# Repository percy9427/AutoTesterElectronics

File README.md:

# AutoTesterElectronics
This contains the Schematics and Board layout for the PCB for the autotester.  The autotester is a machine for automatically testing your water.

Info on the autotester can be found at https://robogardens.com/?p=928.

How you want to generate the PCB is up to you.  I use oshpark.com which requires simply uploading the .brd file.

A video showing the autotester in operation can be found at https://youtu.be/JWSlSH5BVns.

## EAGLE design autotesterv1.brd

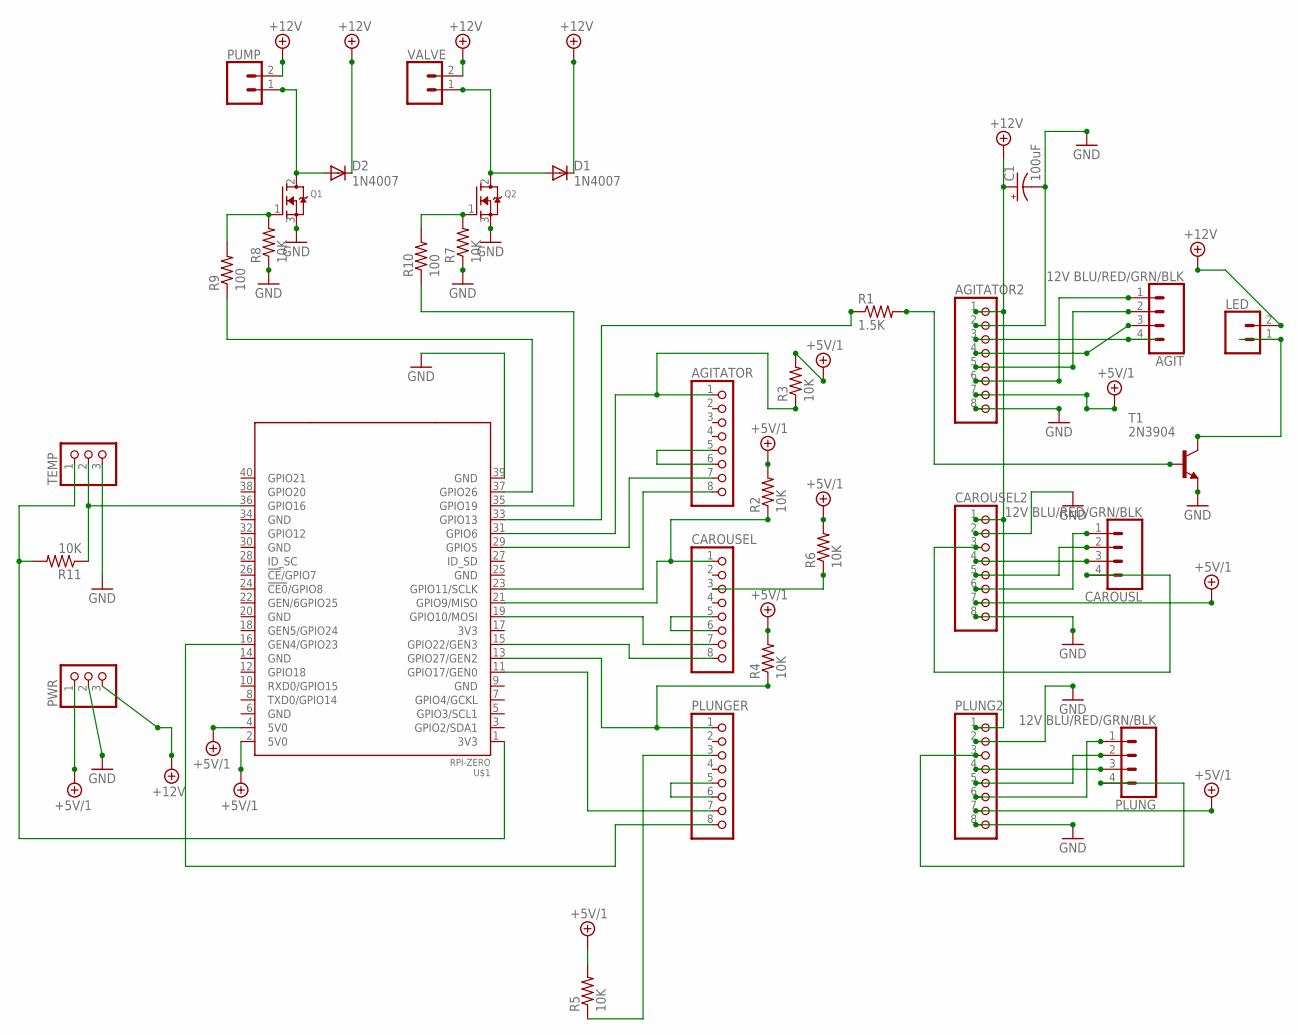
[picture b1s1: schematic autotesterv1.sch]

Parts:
AGIT: 12V BLU/RED/GRN/BLK; SCREWTERMINAL-3.5MM-4
AGITATOR, AGITATOR2: PINHD-1X8; 1X08
C1: 100uF; CPOL-RADIAL-5MM-10MM
CAROUSEL, CAROUSEL2: PINHD-1X8; 1X08
CAROUSL: 12V BLU/RED/GRN/BLK; SCREWTERMINAL-3.5MM-4
D1, D2: 1N4007; DO41-10
LED: CONN_023.5MM; SCREWTERMINAL-3.5MM-2
PLUNG: 12V BLU/RED/GRN/BLK; SCREWTERMINAL-3.5MM-4
PLUNG2: PINHD-1X8; 1X08
PLUNGER: PINHD-1X8; 1X08
PUMP: CONN_023.5MM; SCREWTERMINAL-3.5MM-2
PWR: PINHD-1X3; 1X03
Q1, Q2: MOSFET-NGDS_TO220V; TO220V
R1: 1.5K; 0207/10
R2, R3, R4, R5, R6, R7, R8, R11: 10K; 0207/10
R9, R10: 100; 0207/10
T1: 2N3904; TO92
TEMP: PINHD-1X3; 1X03
U$1: RPI-ZERO; RASPBERRYPI_BASTELSTUBE_V13_RASPI_BOARD_B+_FULL
VALVE: CONN_023.5MM; SCREWTERMINAL-3.5MM-2

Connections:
3V3@1: R11.2, TEMP.1, U$1.1 (3V3)
+5V/1: AGITATOR2.7, CAROUSEL2.7, PLUNG2.7, PWR.1, R2.2, R3.2, R4.2, R5.2, R6.2, U$1.2 (5V0), U$1.4 (5V0)
+12V: AGITATOR2.1, C1.+, CAROUSEL2.1, D1.C, D2.C, LED.2, PLUNG2.1, PUMP.2, PWR.3, VALVE.2
GND: AGITATOR2.2, AGITATOR2.8, C1.-, CAROUSEL2.2, CAROUSEL2.8, PLUNG2.2, PLUNG2.8, PWR.2, Q1.3 (S), Q2.3 (S), R7.1, R8.1, T1.3 (E), TEMP.3, U$1.39 (GND)
unnamed: AGITATOR.1, R3.1, U$1.31 (GPIO6)
unnamed: PLUNGER.8, U$1.16 (GEN4/GPIO23)
unnamed: PLUNGER.3, R5.1
unnamed: AGIT.3, AGITATOR2.4
unnamed: PLUNGER.7, U$1.11 (GPIO17/GEN0)
unnamed: PLUNGER.1, R4.1, U$1.13 (GPIO27/GEN2)
unnamed: AGITATOR.8, U$1.23 (GPIO11/SCLK)
unnamed: CAROUSEL.8, U$1.15 (GPIO22/GEN3)
unnamed: CAROUSEL.7, U$1.19 (GPIO10/MOSI)
unnamed: CAROUSEL.1, R2.1, U$1.21 (GPIO9/MISO)
unnamed: AGIT.2, AGITATOR2.5
unnamed: AGIT.1, AGITATOR2.6
unnamed: AGITATOR.7, U$1.29 (GPIO5)
unnamed: PLUNG.1, PLUNG2.6
unnamed: PLUNG.2, PLUNG2.5
unnamed: CAROUSEL2.6, CAROUSL.1
unnamed: R1.1, U$1.33 (GPIO13)
unnamed: R1.2, T1.2 (B)
unnamed: AGIT.4, AGITATOR2.3
unnamed: LED.1, T1.1 (C)
unnamed: D2.A, PUMP.1, Q1.2 (D)
unnamed: R9.1, U$1.37 (GPIO26)
unnamed: CAROUSEL2.5, CAROUSL.2
unnamed: CAROUSEL2.4, CAROUSL.3
unnamed: CAROUSEL2.3, CAROUSL.4
unnamed: PLUNG.3, PLUNG2.4
unnamed: PLUNG.4, PLUNG2.3
unnamed: Q1.1 (G), R8.2, R9.2
unnamed: CAROUSEL.3, R6.1
unnamed: AGITATOR.5, AGITATOR.6
unnamed: CAROUSEL.5, CAROUSEL.6
unnamed: PLUNGER.5, PLUNGER.6
unnamed: D1.A, Q2.2 (D), VALVE.1
unnamed: R10.1, U$1.35 (GPIO19)
unnamed: Q2.1 (G), R7.2, R10.2
unnamed: R11.1, TEMP.2, U$1.36 (GPIO16)

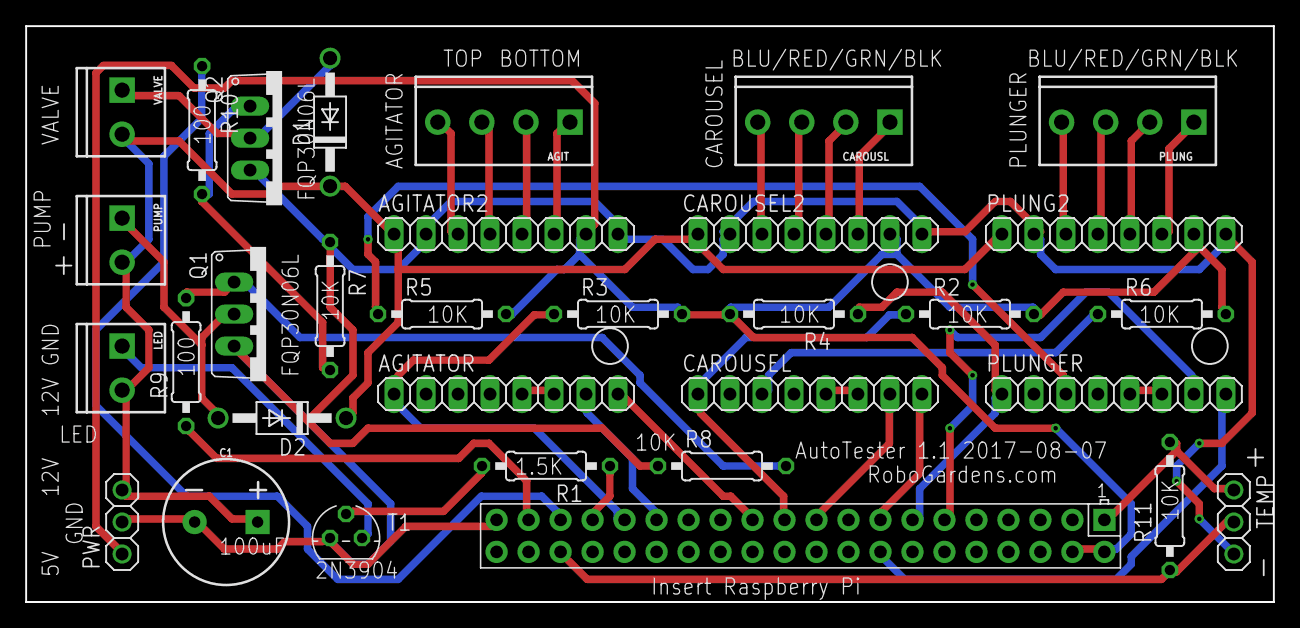
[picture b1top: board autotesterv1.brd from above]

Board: 2 copper layers, 99.1 x 45.7 mm, 32 parts (0 on the bottom side), 40 nets.

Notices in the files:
parts and their libraries:
SparkFun-Connectors: Licensing: Creative Commons ShareAlike 4.0 International - https://creativecommons.org/licenses/by-sa/4.0
